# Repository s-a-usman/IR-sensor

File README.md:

# IR-sensor

A KiCad design files for an IR sensor to be used for a line follower robot. Not  tested yet!

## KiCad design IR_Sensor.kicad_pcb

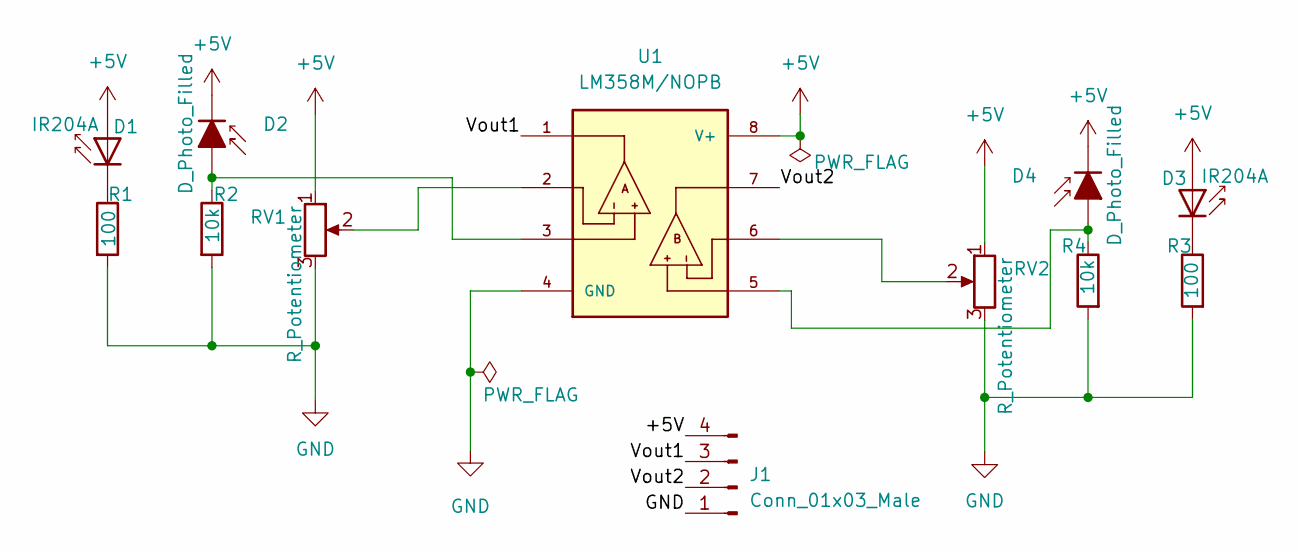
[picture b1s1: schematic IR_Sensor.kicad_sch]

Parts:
D1, D3: IR204A; LED_D3.0mm_IRBlack
D2, D4: D_Photo_Filled; LED_D3.0mm_Clear
J1: Conn_01x03_Male; JST_EH_B4B-EH-A_1x04_P2.50mm_Vertical
R1, R3: 100; R_1210_3225Metric
R2, R4: 10k; R_1210_3225Metric
RV1, RV2: R_Potentiometer; Potentiometer_Bourns_3224J_Horizontal
U1: LM358M/NOPB; SOIC127P599X175-8N

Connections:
+5V: D1.2 (A), D2.1 (K), D3.2 (A), D4.1 (K), J1.4, RV1.1, RV2.1, U1.8 (V+)
/Vout1: J1.3, U1.1
/Vout2: J1.2, U1.7
GND: J1.1, R1.2, R2.2, R3.2, R4.2, RV1.3, RV2.3, U1.4 (GND)
unnamed: D1.1 (K), R1.1
unnamed: D2.2 (A), R2.1, U1.3
unnamed: D3.1 (K), R3.1
unnamed: D4.2 (A), R4.1, U1.5
unnamed: RV1.2, U1.2
unnamed: RV2.2, U1.6

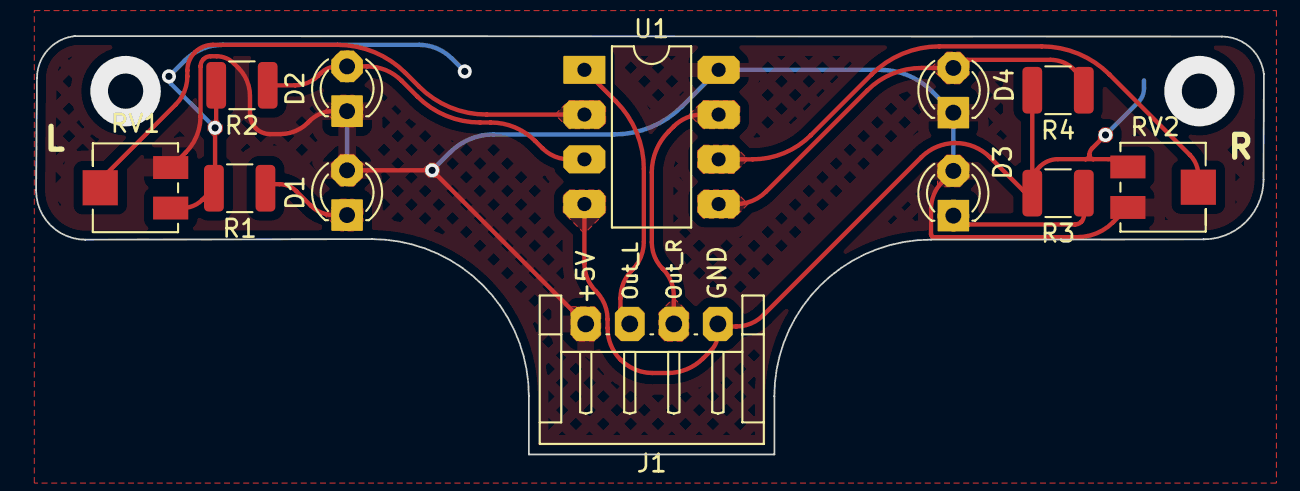
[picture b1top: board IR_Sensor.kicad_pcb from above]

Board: 2 copper layers, 69.7 x 23.7 mm, 12 parts (0 on the bottom side), 10 nets.
